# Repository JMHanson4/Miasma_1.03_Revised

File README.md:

# Miasma_1.03_Revised

***Note: use the BOM included in this repository.*** Some of the components have been relabelled in this revision so the BOM on SinPhi's website is no longer current.

The changes from version 1.03 are:

1) Updated the footprints and symbols to ones included in KiCAD 5.1.5, or otherwise included the auxillary libraries in the repository.

2) Made the 4QX output no longer inverted and added a jumper pin on the back that allows you to switch between (non-inverted) summing and 4QX modes.

3) Added diodes and jumper pins between the cycle gate input and trigger switch for each side. This allows you to choose whether applying a gate to the cycle input will cause it to start cycling automatically (jumper on) or require a trigger to start cycling (jumper off).

4) Fixed the EOC2 output from not being grounded.

5) Small tweaks such as adjusting track spacing, etc.

To do: the resistor in the feedback loop of the 4QX output amp (R67) should be shorted (solder bridge), not 220k. The purpose is to make this output stage a unity gain buffer instead of an amplifier; the 220k will cause the output to clip before the signal peak is reached. If you aren't using the 4QX feature then this is irrelevant.

# Acknowledgements

Original Miasma board by Sin Phi http://www.sinphi.com/synths/miasma/miasma.html, based on the Befaco Rampage http://www.befaco.org/rampage-2/. 4QX and diode mods inspired by Mcop http://www.mcop.co.uk/diy/mods-and-stripboard-layouts/miasma-function-generator-modifications/.

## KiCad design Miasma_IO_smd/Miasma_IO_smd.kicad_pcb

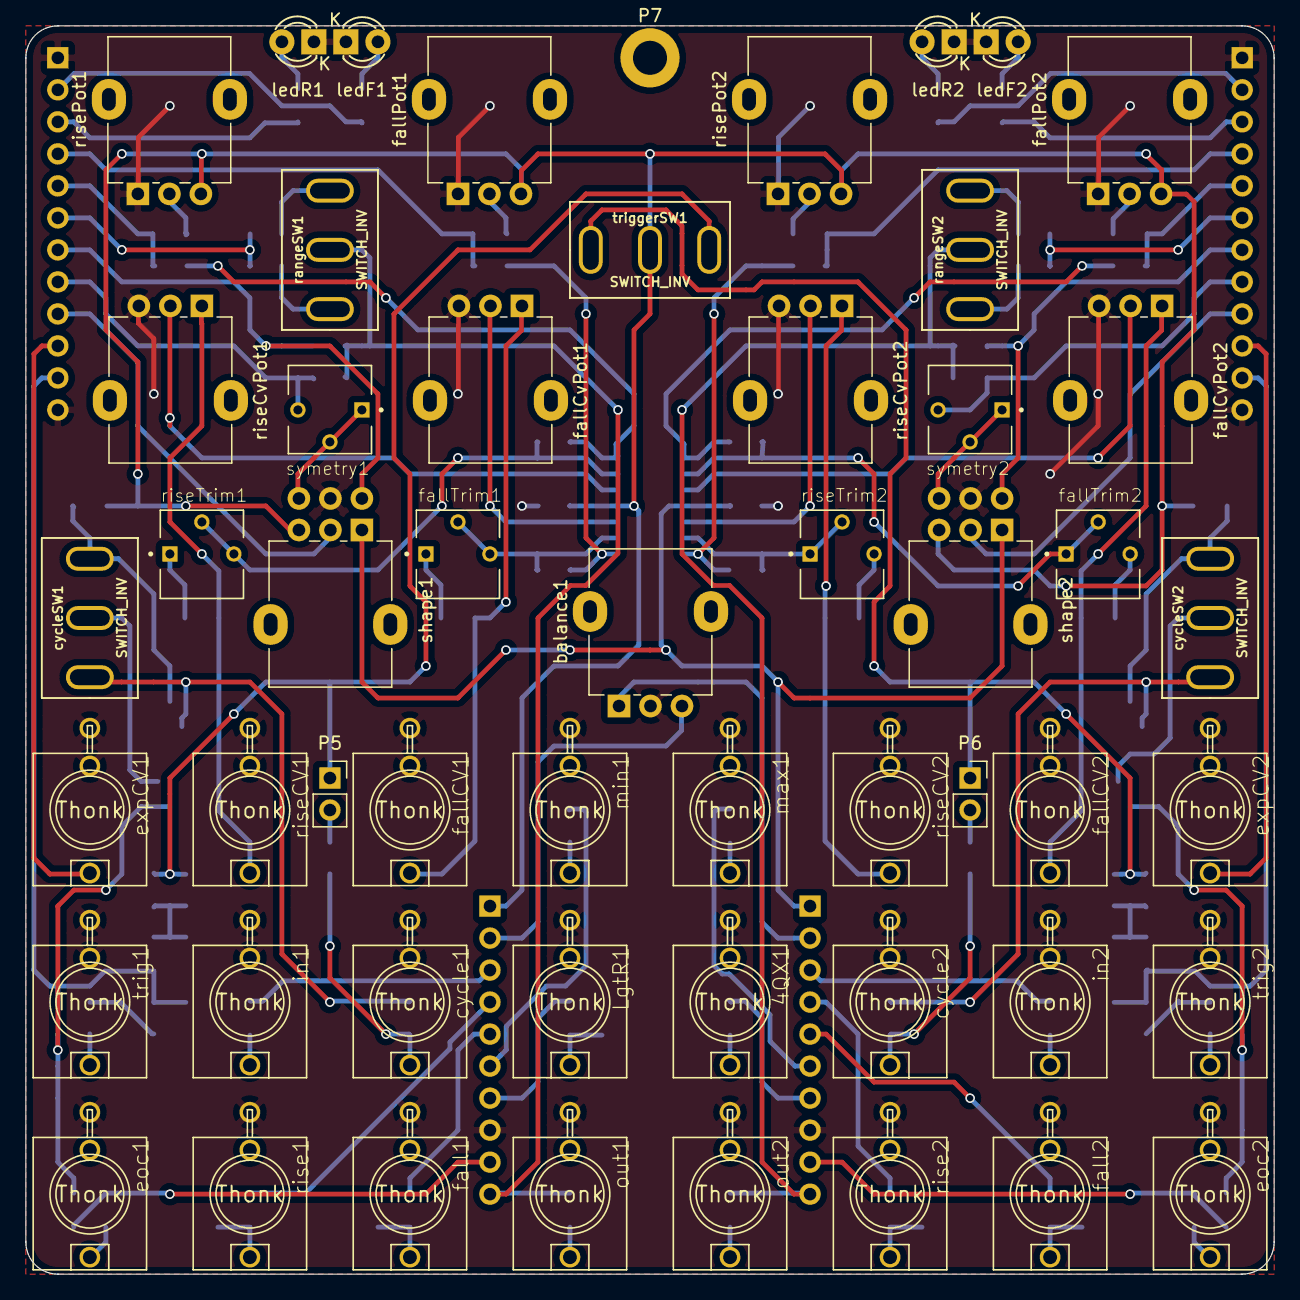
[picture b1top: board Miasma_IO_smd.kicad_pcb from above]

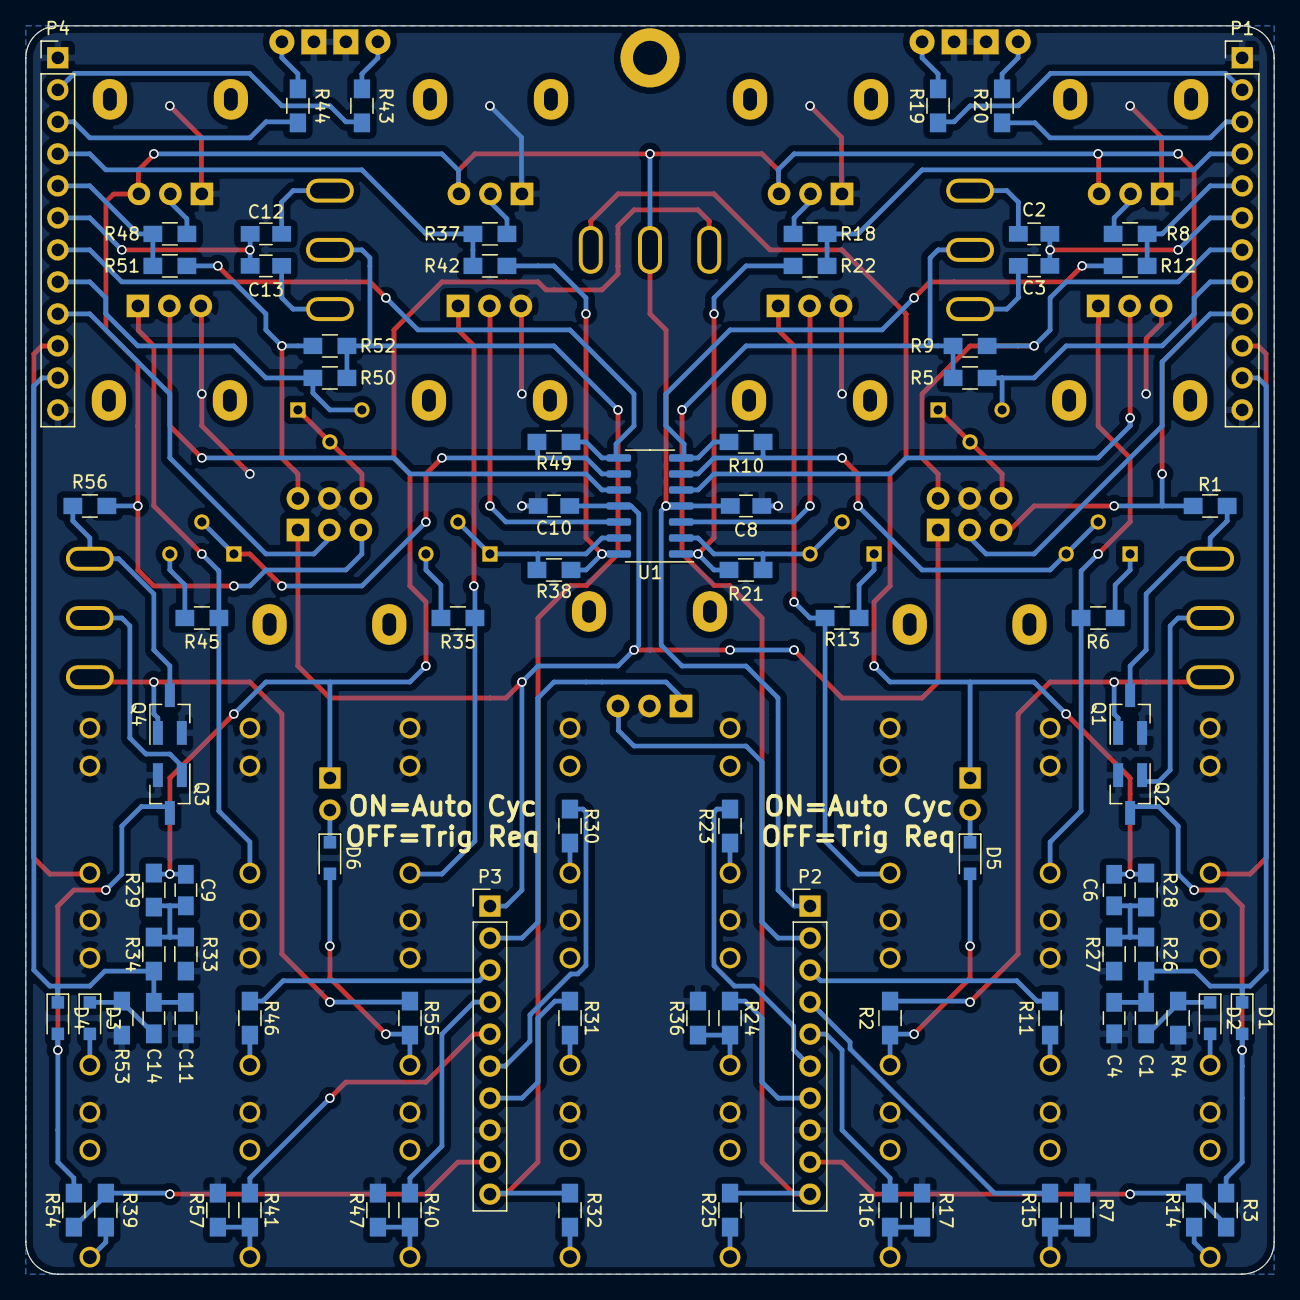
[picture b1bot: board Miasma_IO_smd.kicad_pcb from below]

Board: 2 copper layers, 99.1 x 99.1 mm, 137 parts (84 on the bottom side), 107 nets.

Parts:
4QX1: Thonk; WQP-PJ301M-12_JACK
C1, C4, C11, C14: 10n; C_0805_HandSoldering
C2, C12: 470n; C_0805_HandSoldering
C3, C13: 47n; C_0805_HandSoldering
C6, C9: 100n; C_0805_HandSoldering
C8, C10: 100nF; C_0805_HandSoldering
D1, D2, D3, D4, D5, D6: 1N4148WS; D_SOD-323_HandSoldering
LgtR1: Thonk; WQP-PJ301M-12_JACK
P1, P4: CONN_01X12; PinHeader_1x12_P2.54mm_Vertical
P2, P3: CONN_01X10; PinHeader_1x10_P2.54mm_Vertical
P5, P6: Conn_01x02; PinSocket_1x02_P2.54mm_Vertical
P7: CONN_01X01; MountingHole_2.7mm_M2.5_DIN965_Pad
Q1, Q2, Q3, Q4: MMBT3904; SOT-23_Handsoldering
R1, R3, R4, R27, R33, R53, R54, R56: 10k; R_0805_HandSoldering
R2, R10, R11, R12, R21, R22, R38, R42, R46, R49, R51, R55: 100k; R_0805_HandSoldering
R5, R9, R50, R52: 23k7; R_0805_HandSoldering
R6, R13, R35, R45: 47k; R_0805_HandSoldering
R7, R17, R36, R47, R57: 1M; R_0805_HandSoldering
R8, R18, R37, R48: 110k; R_0805_HandSoldering
R14, R15, R16, R23, R24, R25, R26, R30, R31, R32, R34, R39, R40, R41: 1k; R_0805_HandSoldering
R19, R20, R43, R44: 2k2; R_0805_HandSoldering
R28, R29: 4M7; R_0805_HandSoldering
U1: TL074; SOIC-14_3.9x8.7mm_P1.27mm
balance1: 1M; Potentiometer_Alpha_RD901F-40-00D_Single_Vertical
cycle1, cycle2: Thonk; WQP-PJ301M-12_JACK
cycleSW1, cycleSW2: SWITCH_INV; SPDT_Switch_P4.7mm
eoc1, eoc2: Thonk; WQP-PJ301M-12_JACK
expCV1, expCV2: Thonk; WQP-PJ301M-12_JACK
fall1, fall2: Thonk; WQP-PJ301M-12_JACK
fallCV1, fallCV2: Thonk; WQP-PJ301M-12_JACK
fallCvPot1, fallCvPot2: 100k; Potentiometer_Alpha_RD901F-40-00D_Single_Vertical
fallPot1, fallPot2: 100k; Potentiometer_Alpha_RD901F-40-00D_Single_Vertical
fallTrim1, fallTrim2: 100k; Bourns_3362P
in1, in2: Thonk; WQP-PJ301M-12_JACK
ledF1, ledF2: LED; LED-3MM
ledR1, ledR2: LED; LED-3MM
max1: Thonk; WQP-PJ301M-12_JACK
min1: Thonk; WQP-PJ301M-12_JACK
out1, out2: Thonk; WQP-PJ301M-12_JACK
rangeSW1, rangeSW2: SWITCH_INV; SPDT_Switch_P4.7mm
rise1, rise2: Thonk; WQP-PJ301M-12_JACK
riseCV1, riseCV2: Thonk; WQP-PJ301M-12_JACK
riseCvPot1, riseCvPot2: 100k; Potentiometer_Alpha_RD901F-40-00D_Single_Vertical
risePot1, risePot2: 100k; Potentiometer_Alpha_RD901F-40-00D_Single_Vertical
riseTrim1, riseTrim2: 100k; Bourns_3362P
shape1, shape2: 10K; Potentiometer_Alpha_RD902F-40-00D_Dual_Vertical
symetry1, symetry2: 10k; Bourns_3362P
trig1, trig2: Thonk; WQP-PJ301M-12_JACK
triggerSW1: SWITCH_INV; SPDT_Switch_P4.7mm

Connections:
4QX: P3.7, R31.1
EOC1: P2.9, R3.1, R14.2
EOC2: P3.9, R39.2, R54.1
Exp1: P1.10, expCV1.P$1
Exp2: P4.10, expCV2.P$1
Fall1: P2.5, R16.1
Fall2: P3.5, R41.1
FallCv1: P1.4, R18.2, R22.2
FallCv2: P4.5, R48.2, R51.2
GND: 4QX1.P$3, C4.2, C8.2, C10.2, C11.2, LgtR1.P$3, P1.1, P1.12, P2.8, P3.8, P4.1, P4.12, Q1.2, Q2.2, Q3.2, Q4.2, R4.2, R7.2, R17.2, R27.1, R33.1, R36.2, R47.2, R53.2, R57.2, balance1.2, cycle1.P$2, cycle1.P$3, cycle2.P$2, cycle2.P$3, eoc1.P$3, eoc2.P$3, expCV1.P$2, expCV1.P$3, expCV2.P$2, expCV2.P$3, fall1.P$3, fall2.P$3, fallCV1.P$2, fallCV1.P$3, fallCV2.P$2, fallCV2.P$3, fallCvPot1.3, fallCvPot2.3, fallPot1.1, fallPot2.1, in1.P$2, in1.P$3, in2.P$2, in2.P$3, ledF1.1, ledF2.1, ledR1.1, ledR2.1, max1.P$3, min1.P$3, out1.P$3, out2.P$3, rise1.P$3, rise2.P$3, riseCV1.P$2, riseCV1.P$3, riseCV2.P$2, riseCV2.P$3, riseCvPot1.3, riseCvPot2.3, risePot1.1, risePot2.1, shape1.5, shape2.5, trig1.P$2, trig1.P$3, trig2.P$2, trig2.P$3
In1: P2.3, R11.1
In2: P3.3, R46.1
L>R: P2.7, R24.1
Max: P3.6, R30.1
Min: P2.6, R23.1
unnamed: 4QX1.P$1, R31.2
unnamed: C1.1, D2.1, R4.1
unnamed: C2.2, rangeSW1.3
unnamed: C3.2, rangeSW1.1
unnamed: C6.2, R26.2, R27.2, R28.1
unnamed: C9.2, R29.1, R33.2, R34.2
unnamed: C12.2, rangeSW2.3
unnamed: C13.2, rangeSW2.1
unnamed: C14.1, D3.1, R53.1
unnamed: D1.2, Q2.3, R3.2
unnamed: D2.2, trig1.P$1
unnamed: D3.2, trig2.P$1
unnamed: D4.2, Q3.3, R54.2
unnamed: D5.1, P5.2
unnamed: D5.2, R2.2, cycle1.P$1
unnamed: D6.1, P6.2
unnamed: D6.2, R55.2, cycle2.P$1
unnamed: LgtR1.P$1, R24.2, R36.1
unnamed: P1.2, R19.1
unnamed: P1.3, R20.1
unnamed: P2.2, balance1.3
unnamed: P3.2, balance1.1
unnamed: P4.2, R43.1
unnamed: P4.3, R44.1
unnamed: Q1.1, R2.1, cycleSW1.1
unnamed: Q1.3, R1.2, cycleSW1.3
unnamed: Q2.1, cycleSW1.2
unnamed: Q3.1, cycleSW2.2
unnamed: Q4.1, R55.1, cycleSW2.1
unnamed: Q4.3, R56.2, cycleSW2.3
unnamed: R6.1, riseTrim1.1
unnamed: R6.2, riseCV1.P$1, riseCvPot1.1
unnamed: R8.1, risePot1.2
unnamed: R10.1, R12.1, U1.7
unnamed: R10.2, U1.6, riseTrim1.2, riseTrim1.3
unnamed: R11.2, in1.P$1
unnamed: R13.1, fallTrim1.1
unnamed: R13.2, fallCV1.P$1, fallCvPot1.1
unnamed: R14.1, eoc1.P$1
unnamed: R7.1, R15.1, rise1.P$1
unnamed: R16.2, R17.1, fall1.P$1
unnamed: R18.1, fallPot1.2
unnamed: R19.2, ledF1.2
unnamed: R20.2, ledR1.2
unnamed: R21.1, R22.1, U1.1
unnamed: R21.2, U1.2, fallTrim1.2, fallTrim1.3
unnamed: R23.2, min1.P$1
unnamed: R25.1, out1.P$1
unnamed: R30.2, max1.P$1
unnamed: R32.1, out2.P$1
unnamed: R35.1, riseTrim2.3
unnamed: R35.2, riseCV2.P$1, riseCvPot2.1
unnamed: R37.1, risePot2.2
unnamed: R38.1, R42.1, U1.14
unnamed: R38.2, U1.13, riseTrim2.1, riseTrim2.2
unnamed: R39.1, eoc2.P$1
unnamed: R40.2, R47.1, rise2.P$1
unnamed: R41.2, R57.1, fall2.P$1
unnamed: R43.2, ledR2.2
unnamed: R44.2, ledF2.2
unnamed: R45.1, fallTrim2.3
unnamed: R45.2, fallCV2.P$1, fallCvPot2.1
unnamed: R46.2, in2.P$1
unnamed: R48.1, fallPot2.2
unnamed: R49.1, R51.1, U1.8
unnamed: R49.2, U1.9, fallTrim2.1, fallTrim2.2
unnamed: U1.3, fallCvPot1.2
unnamed: U1.5, riseCvPot1.2
unnamed: U1.10, fallCvPot2.2
unnamed: U1.12, riseCvPot2.2
unnamed: shape1.6, symetry1.1, symetry1.2
unnamed: shape2.6, symetry2.1, symetry2.2
Out1: P2.10, R5.2, R9.2, R25.2, rangeSW1.2
Out2: P3.10, R32.2, R50.2, R52.2, rangeSW2.2
Rise1: P2.4, R15.2
Rise2: P3.4, R40.1
RiseCv1: P1.5, R8.2, R12.2
RiseCv2: P4.4, R37.2, R42.2
RngCap1: C2.1, C3.1, P1.6
RngCap2: C12.1, C13.1, P4.6
Sym1_1: P1.7, R9.1, shape1.4
Sym1_2: P4.7, R52.1, shape2.4
Sym2_1: P1.9, shape1.2
Sym2_2: P4.9, shape2.2
Sym3_1: P1.8, R5.1, symetry1.3
Sym3_2: P4.8, R50.1, symetry2.3
TRIG_SW1: C6.1, P5.1, R28.2, triggerSW1.3
TRIG_SW2: C9.1, P6.1, R29.2, triggerSW1.1
Trig1: C1.2, C4.1, D1.1, P1.11, R26.1
Trig2: C11.1, C14.2, D4.1, P4.11, R34.1
VCC: C8.1, P2.1, R1.1, R56.1, U1.4, fallPot1.3, fallPot2.3, risePot1.3, risePot2.3, shape1.3, shape2.3, triggerSW1.2
VEE: C10.1, P3.1, U1.11, shape1.1, shape2.1

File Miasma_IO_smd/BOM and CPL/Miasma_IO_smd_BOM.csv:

Comment,Designator,Footprint
SWITCH_INV,"cycleSW1,cycleSW2,rangeSW1,rangeSW2,triggerSW1",SPDT_Switch_P4.7mm
MMBT3904,"Q4,Q3,Q2,Q1",SOT-23_Handsoldering
10k,"symetry2,symetry1",Bourns_3362P
100k,"riseTrim2,riseTrim1,fallTrim2,fallTrim1",Bourns_3362P
Thonk,"trig2,trig1,riseCV2,riseCV1,rise2,rise1,out2,out1,min1,max1,LgtR1,in2,in1,fallCV2,fallCV1,fall2,fall1,expCV2,expCV1,eoc2,eoc1,cycle2,cycle1,4QX1",WQP-PJ301M-12_JACK
10K,"shape2,shape1",Potentiometer_Alpha_RD902F-40-00D_Dual_Vertical
100k,"risePot2,risePot1,riseCvPot2,riseCvPot1,fallPot2,fallPot1,fallCvPot2,fallCvPot1",Potentiometer_Alpha_RD901F-40-00D_Single_Vertical
1M,balance1,Potentiometer_Alpha_RD901F-40-00D_Single_Vertical
Conn_01x02,"P6,P5",PinSocket_1x02_P2.54mm_Vertical
1N4148WS,"D6,D5,D4,D3,D2,D1",D_SOD-323_HandSoldering
TL074,U1,SOIC-14_3.9x8.7mm_P1.27mm
CONN_01X12,"P4,P1",PinHeader_1x12_P2.54mm_Vertical
CONN_01X10,"P3,P2",PinHeader_1x10_P2.54mm_Vertical
LED,"ledF1,ledF2,ledR1,ledR2",LED-3MM
CONN_01X01,P7,MountingHole_2.7mm_M2.5_DIN965_Pad
10k,"R56,R54,R53,R33,R27,R4,R3,R1",R_0805_HandSoldering
100k,"R55,R51,R49,R46,R42,R38,R22,R21,R12,R11,R10,R2",R_0805_HandSoldering
23k7,"R52,R50,R9,R5",R_0805_HandSoldering
110k,"R48,R37,R18,R8",R_0805_HandSoldering
47k,"R45,R35,R13,R6",R_0805_HandSoldering
2k2,"R44,R43,R20,R19",R_0805_HandSoldering
1k,"R41,R40,R39,R34,R32,R31,R30,R26,R25,R24,R23,R16,R15,R14",R_0805_HandSoldering
4M7,"R29,R28",R_0805_HandSoldering
10n,"C14,C11,C4,C1",C_0805_HandSoldering
47n,"C13,C3",C_0805_HandSoldering
470n,"C12,C2",C_0805_HandSoldering
100n,"C9,C6",C_0805_HandSoldering
100nF,"C10,C8",C_0805_HandSoldering
1M,"R7,R17,R36,R47,R57",R_0805_HandSoldering

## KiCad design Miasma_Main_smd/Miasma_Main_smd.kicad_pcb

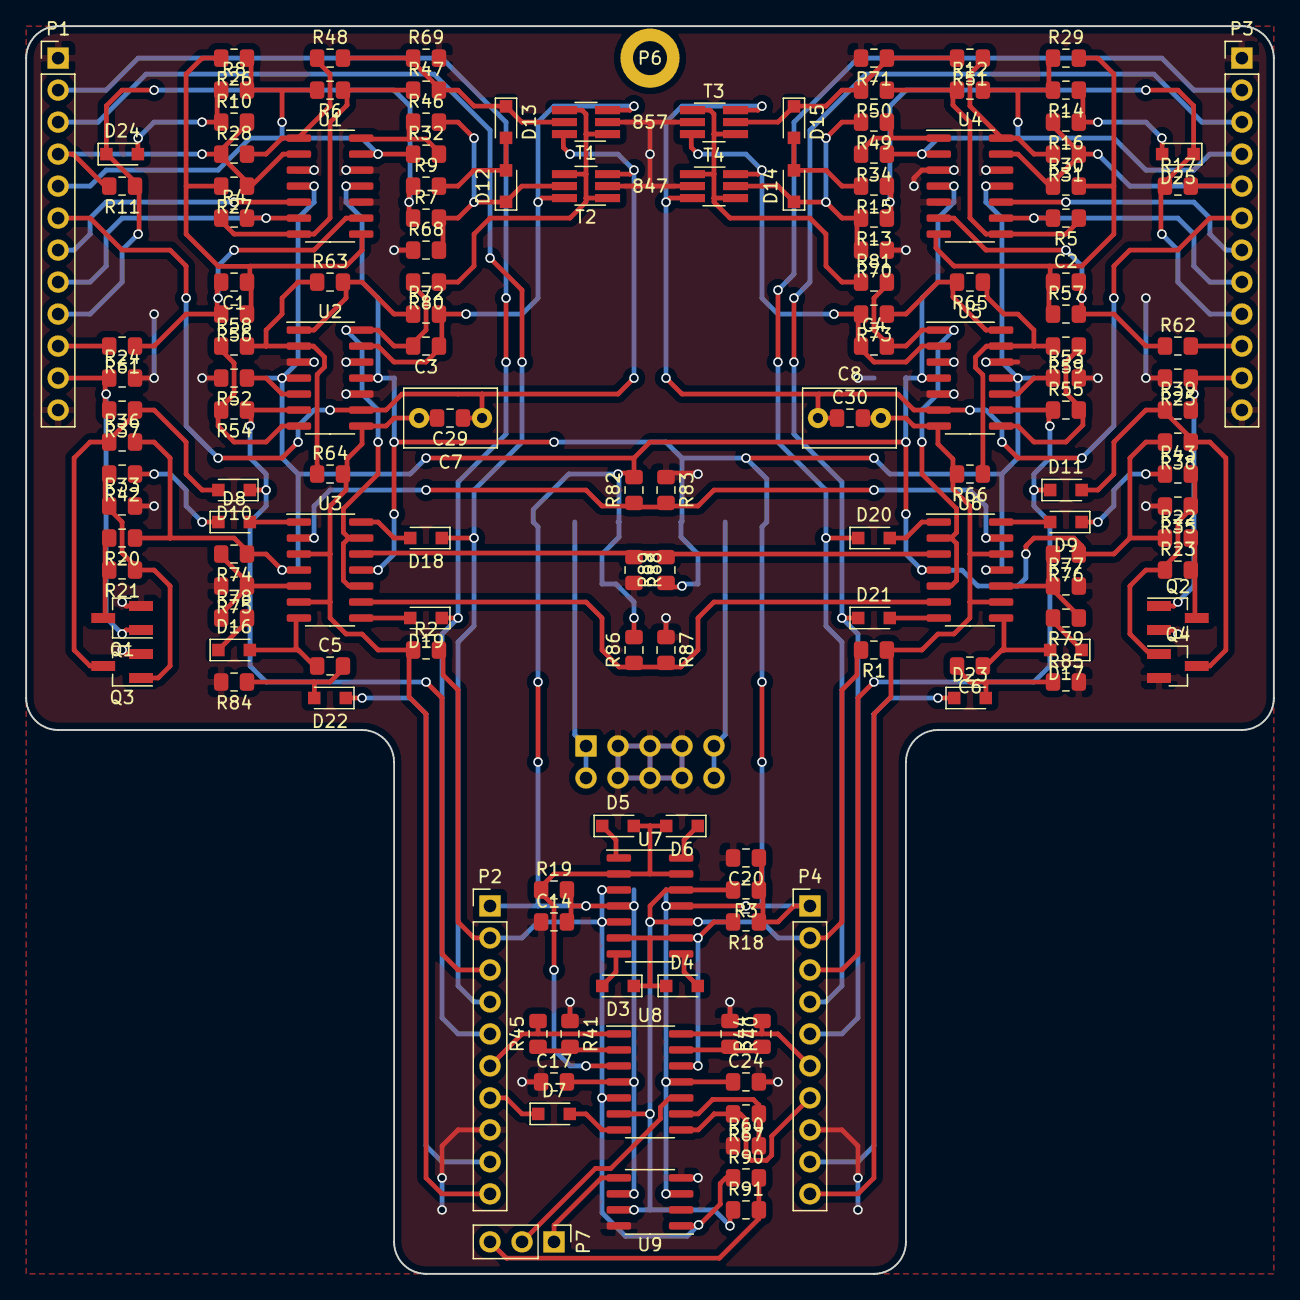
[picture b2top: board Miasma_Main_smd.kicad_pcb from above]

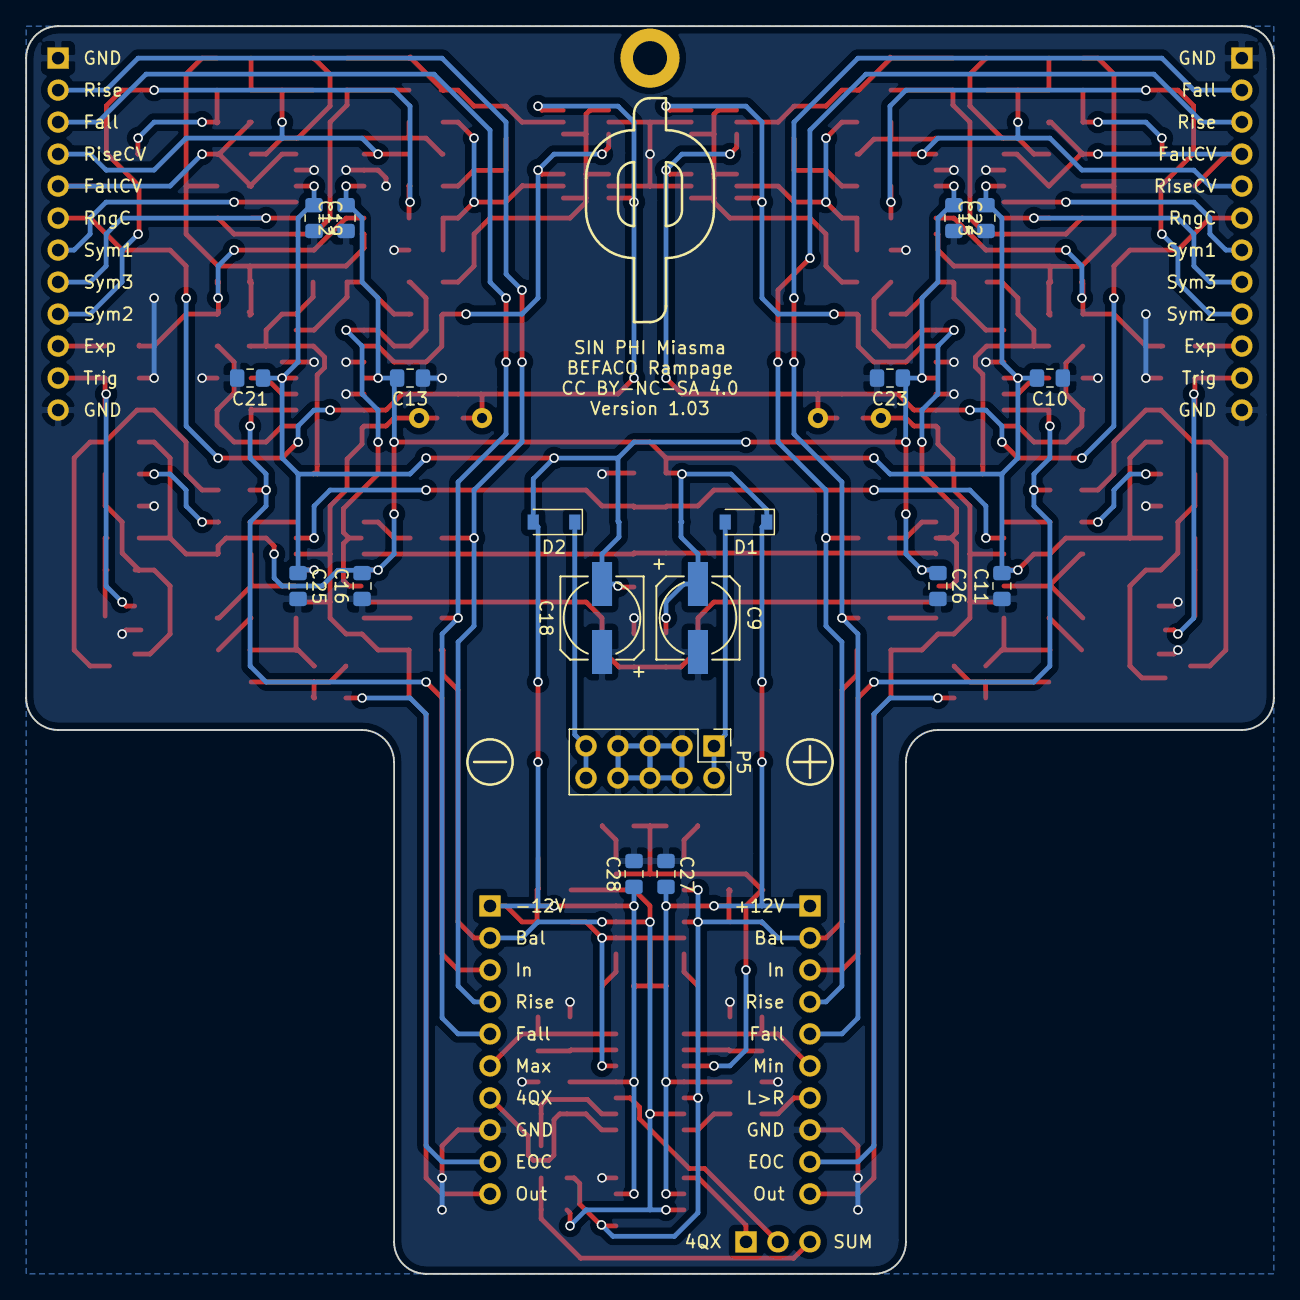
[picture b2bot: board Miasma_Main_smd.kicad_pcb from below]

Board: 2 copper layers, 99.1 x 99.1 mm, 170 parts (19 on the bottom side), 107 nets.

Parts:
C1, C2: 560p; C_0805_2012Metric_Pad1.15x1.40mm_HandSolder
C3, C4: 100p; C_0805_2012Metric_Pad1.15x1.40mm_HandSolder
C5, C6, C10, C11, C12, C13, C14, C15, C16, C17, C19, C20, C21, C22, C23, C24, C25, C26, C27, C28: 100n; C_0805_2012Metric_Pad1.15x1.40mm_HandSolder
C7, C8: 2n2 (PP); C_Rect_L7.2mm_W4.5mm_P5.00mm_FKS2_FKP2_MKS2_MKP2
C9, C18: 10u; c_elec_6.3x5.8
C29, C30: 1n; C_0805_2012Metric_Pad1.15x1.40mm_HandSolder
D1, D2: 1N5819HW; D_SOD-123
D3, D4, D5, D6, D7, D8, D9, D10, D11, D12, D13, D14, D15, D16, D17, D18, D19, D20, D21, D22, D23, D24, D25: 1N4148WS; D_SOD-323_HandSoldering
P1, P3: CONN_01X12; PinHeader_1x12_P2.54mm_Vertical
P2, P4: CONN_01X10; PinHeader_1x10_P2.54mm_Vertical
P5: CONN_02X05; PinHeader_2x05_P2.54mm_Vertical
P6: CONN_01X01; MountingHole_2.7mm_M2.5_DIN965_Pad
P7: SUM_or_4QX; PinHeader_1x03_P2.54mm_Vertical
Q1, Q2, Q3, Q4: MMBT3904; SOT-23_Handsoldering
R1, R2, R40, R41: 30k; R_0805_2012Metric_Pad1.15x1.40mm_HandSolder
R3: 10M; R_0805_2012Metric_Pad1.15x1.40mm_HandSolder
R4, R5, R21, R23, R37, R39, R42, R43, R44, R45, R58, R59, R64, R66, R86, R89: 10k; R_0805_2012Metric_Pad1.15x1.40mm_HandSolder
R6, R12, R26, R27, R28, R29, R30, R31, R32, R33, R34, R35, R46, R47, R48, R49, R50, R51, R52, R53, R54, R55, R56, R57, R60, R78, R79, R83, R90, R91: 100k; R_0805_2012Metric_Pad1.15x1.40mm_HandSolder
R7, R11, R13, R17, R24, R25: 560k; R_0805_2012Metric_Pad1.15x1.40mm_HandSolder
R8, R10, R14, R16: 3M; R_0805_2012Metric_Pad1.15x1.40mm_HandSolder
R9, R15, R18, R19, R74, R76: 1M; R_0805_2012Metric_Pad1.15x1.40mm_HandSolder
R20, R22, R36, R38: 4k7; R_0805_2012Metric_Pad1.15x1.40mm_HandSolder
R61, R62, R80, R81: 110k; R_0805_2012Metric_Pad1.15x1.40mm_HandSolder
R63, R65: 180k; R_0805_2012Metric_Pad1.15x1.40mm_HandSolder
R67: 220k; R_0805_2012Metric_Pad1.15x1.40mm_HandSolder
R68, R69, R70, R71: 2k2; R_0805_2012Metric_Pad1.15x1.40mm_HandSolder
R72, R73: 470k; R_0805_2012Metric_Pad1.15x1.40mm_HandSolder
R75, R77: 22k; R_0805_2012Metric_Pad1.15x1.40mm_HandSolder
R82: 20k; R_0805_2012Metric_Pad1.15x1.40mm_HandSolder
R84, R85, R87, R88: 1k; R_0805_2012Metric_Pad1.15x1.40mm_HandSolder
T1, T3: BCM857DS; TSOT-23-6_HandSoldering
T2, T4: BCM847DS; TSOT-23-6_HandSoldering
U1, U2, U3, U4, U5, U6, U7, U8: TL074; SOIC-14_3.9x8.7mm_P1.27mm
U9: AD633; SOIC-8_3.9x4.9mm_P1.27mm

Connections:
4QX: P4.7, R67.2, U8.8
+1.2V: R86.1, R87.2, U3.9, U6.6
+2.4V: R82.1, R83.2, U3.2, U6.13
-1.2V: R88.1, R89.2, U3.12, U6.3
Bal1: P2.2, R2.2, R90.1, U7.3, U7.5, U8.5, U9.1
Bal2: P4.2, R1.2, R3.2, R91.1, U7.10, U7.12, U8.6, U9.7
EOC1: D22.1, P2.9
EOC2: D23.1, P4.9
Exp1: P1.10, R61.2
Exp2: P3.10, R62.2
Fall1: D19.1, P1.2, P2.5
Fall2: D21.1, P3.3, P4.5
FallCv1: P1.4, R10.2, R11.2, R27.1, R28.1, U1.2
FallCv2: P3.5, R16.2, R17.2, R30.1, R31.1, U4.13
GND: C9.2, C10.1, C11.1, C12.1, C13.1, C14.1, C15.1, C16.1, C17.1, C18.1, C19.2, C20.2, C21.2, C22.2, C23.2, C24.2, C25.2, C26.2, C27.1, C28.2, P1.1, P1.12, P2.8, P3.1, P3.12, P4.8, P5.3, P5.4, P5.5, P5.6, P5.7, P5.8, Q1.2, Q2.2, Q3.2, Q4.2, R24.2, R25.2, R33.2, R35.2, R40.1, R41.1, R52.2, R53.2, R60.1, R68.1, R69.2, R70.1, R71.2, R75.2, R77.2, R83.1, R84.2, R85.2, R87.1, R88.2, T1.2, T2.2, T3.2, T4.2, U1.3, U1.10, U1.12, U2.3, U2.10, U2.12, U4.3, U4.5, U4.12, U5.3, U5.5, U5.12, U9.2, U9.4, U9.8
In1: D10.1, P2.3, R54.1, U2.6
In2: D11.1, P4.3, R55.1, U5.9
L>R: D7.1, P2.7
Max: P4.6, R44.2, U8.14
Min: P2.6, R45.2, U8.1
unnamed: C1.1, R26.2, R27.2, R56.1, U1.8
unnamed: C1.2, R56.2, R61.1, U1.9
unnamed: C2.1, R29.2, R30.2, R57.1, U4.7
unnamed: C2.2, R57.2, R62.1, U4.6
unnamed: C3.1, R72.2, T1.3, T2.6, U2.13
unnamed: C3.2, R80.2, U2.14, U3.10, U3.13
unnamed: C4.1, R73.2, T3.3, T4.6, U5.2
unnamed: C4.2, R81.2, U5.1, U6.2, U6.5
unnamed: C5.1, D16.2, U3.7
unnamed: C5.2, D22.2, R84.1
unnamed: C6.1, D17.2, U6.8
unnamed: C6.2, D23.2, R85.1
unnamed: D1.2, P5.1, P5.2
unnamed: D2.1, P5.9, P5.10
unnamed: D3.1, D4.1, R18.2, U7.6, U7.9, U8.12
unnamed: D3.2, U7.7
unnamed: D4.2, U7.8
unnamed: D5.1, U7.1
unnamed: D5.2, D6.2, R19.1, U7.2, U7.13, U8.3
unnamed: D6.1, U7.14
unnamed: D7.2, U8.7
unnamed: D8.1, R42.1
unnamed: D8.2, U3.1
unnamed: D9.1, R43.1
unnamed: D9.2, U6.14
unnamed: D10.2, Q3.3, R36.1, R37.1
unnamed: D11.2, Q4.3, R38.1, R39.1
unnamed: D12.1, R7.2, R46.2, R68.2, T2.5
unnamed: D12.2, D13.2, R9.2
unnamed: D13.1, R47.2, R48.2, R69.1, T1.5
unnamed: D14.1, R13.2, R49.2, R70.2, T4.5
unnamed: D14.2, D15.2, R15.2
unnamed: D15.1, R50.2, R51.2, R71.1, T3.5
unnamed: D16.1, R78.2
unnamed: D17.1, R79.2
unnamed: D18.2, U3.14
unnamed: D19.2, U3.8
unnamed: D20.2, U6.1
unnamed: D21.2, U6.7
unnamed: D24.2, R8.1, R10.1
unnamed: D25.2, R14.1, R16.1
unnamed: P7.1, U9.5
unnamed: P7.2, U8.10
unnamed: P7.3, R90.2, R91.2
unnamed: Q1.3, R20.2, R21.2
unnamed: Q2.3, R22.2, R23.2
unnamed: Q3.1, R21.1, R33.1, R42.2
unnamed: Q4.1, R23.1, R35.1, R43.2
unnamed: R4.1, R6.1, R47.1, U1.7
unnamed: R5.1, R12.1, R50.1, U4.8
unnamed: R28.2, R48.1, U1.1
unnamed: R31.2, R51.1, U4.14
unnamed: R32.2, R46.1, U1.14
unnamed: R34.2, R49.1, U4.1
unnamed: R40.2, R44.1, U8.13
unnamed: R41.2, R45.1, U8.2
unnamed: R52.1, U2.5
unnamed: R53.1, U5.10
unnamed: R54.2, R58.1, U2.7
unnamed: R55.2, R59.1, U5.8
unnamed: R58.2, R63.1, R64.1, U2.2
unnamed: R59.2, R65.1, R66.1, U5.13
unnamed: R60.2, R67.1, U8.9
unnamed: R63.2, R72.1, U2.1
unnamed: R65.2, R73.1, U5.14
unnamed: R74.2, R75.1, R78.1, U3.5
unnamed: R76.2, R77.1, R79.1, U6.10
unnamed: R80.1, T1.1, T1.4, T2.1, T2.4
unnamed: R81.1, T3.1, T3.4, T4.1, T4.4
Out1: C7.2, C29.2, P2.10, R2.1, R64.2, U2.8, U3.3, U3.6
Out2: C8.2, C30.2, P4.10, R1.1, R66.2, U5.7, U6.9, U6.12
Rise1: D18.1, P1.3, P2.4
Rise2: D20.1, P3.2, P4.4
RiseCv1: P1.5, R6.2, R8.2, R26.1, R32.1, U1.13
RiseCv2: P3.4, R12.2, R14.2, R29.1, R34.1, U4.2
RngCap1: C7.1, C29.1, P1.6, T1.6, T2.3, U2.9
RngCap2: C8.1, C30.1, P3.6, T3.6, T4.3, U5.6
Sym1_1: P1.7, U1.5
Sym1_2: P3.7, U4.10
Sym2_1: D24.1, P1.9, R7.1, R9.1, R11.1
Sym2_2: D25.1, P3.9, R13.1, R15.1, R17.1
Sym3_1: P1.8, R4.2, U1.6
Sym3_2: P3.8, R5.2, U4.9
Trig: P3.11, Q2.1, R25.1, R39.2
Trig1: P1.11, Q1.1, R24.1, R37.2
VCC: C9.1, C10.2, C11.2, C12.2, C13.2, C14.2, C15.2, C16.2, C17.2, C27.2, D1.1, P2.1, R19.2, R20.1, R22.1, R36.2, R38.2, R74.1, R76.1, R82.2, R86.2, U1.4, U2.4, U3.4, U4.4, U5.4, U6.4, U7.4, U8.4, U9.6
VEE: C18.2, C19.1, C20.1, C21.1, C22.1, C23.1, C24.1, C25.1, C26.1, C28.1, D2.2, P4.1, R3.1, R18.1, R89.1, U1.11, U2.11, U3.11, U4.11, U5.11, U6.11, U7.11, U8.11, U9.3

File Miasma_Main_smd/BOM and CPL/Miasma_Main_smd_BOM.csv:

Comment,Designator,Footprint
BCM847DS,"T4,T2",TSOT-23-6_HandSoldering
BCM857DS,"T3,T1",TSOT-23-6_HandSoldering
MMBT3904,"Q4,Q3,Q2,Q1",SOT-23_Handsoldering
AD633,U9,SOIC-8_3.9x4.9mm_P1.27mm
1N4148WS,"D23,D22,D21,D20,D19,D18,D17,D16,D15,D14,D13,D12,D11,D10,D9,D8,D7,D6,D5,D4,D3,D25,D24",D_SOD-323_HandSoldering
TL074,"U8,U7,U6,U5,U4,U3,U2,U1",SOIC-14_3.9x8.7mm_P1.27mm
100k,"R91,R90,R83,R79,R78,R60,R57,R56,R55,R54,R53,R52,R51,R50,R49,R48,R47,R46,R35,R34,R33,R32,R31,R30,R29,R28,R27,R26,R12,R6",R_0805_2012Metric_Pad1.15x1.40mm_HandSolder
10k,"R89,R86,R66,R64,R59,R58,R45,R44,R43,R42,R39,R37,R23,R21,R5,R4",R_0805_2012Metric_Pad1.15x1.40mm_HandSolder
1k,"R88,R87,R85,R84",R_0805_2012Metric_Pad1.15x1.40mm_HandSolder
20k,R82,R_0805_2012Metric_Pad1.15x1.40mm_HandSolder
110k,"R81,R80,R62,R61",R_0805_2012Metric_Pad1.15x1.40mm_HandSolder
22k,"R77,R75",R_0805_2012Metric_Pad1.15x1.40mm_HandSolder
1M,"R76,R74,R19,R18,R15,R9",R_0805_2012Metric_Pad1.15x1.40mm_HandSolder
470k,"R73,R72",R_0805_2012Metric_Pad1.15x1.40mm_HandSolder
2k2,"R71,R70,R69,R68",R_0805_2012Metric_Pad1.15x1.40mm_HandSolder
220k,R67,R_0805_2012Metric_Pad1.15x1.40mm_HandSolder
180k,"R65,R63",R_0805_2012Metric_Pad1.15x1.40mm_HandSolder
30k,"R41,R40,R2,R1",R_0805_2012Metric_Pad1.15x1.40mm_HandSolder
4k7,"R38,R36,R22,R20",R_0805_2012Metric_Pad1.15x1.40mm_HandSolder
560k,"R25,R24,R17,R13,R11,R7",R_0805_2012Metric_Pad1.15x1.40mm_HandSolder
3M,"R16,R14,R10,R8",R_0805_2012Metric_Pad1.15x1.40mm_HandSolder
10M,R3,R_0805_2012Metric_Pad1.15x1.40mm_HandSolder
SUM_or_4QX,P7,PinHeader_1x03_P2.54mm_Vertical
1n,"C30,C29",C_0805_2012Metric_Pad1.15x1.40mm_HandSolder
100n,"C28,C27,C26,C25,C24,C23,C22,C21,C20,C19,C17,C16,C15,C14,C13,C12,C11,C10,C6,C5",C_0805_2012Metric_Pad1.15x1.40mm_HandSolder
100p,"C4,C3",C_0805_2012Metric_Pad1.15x1.40mm_HandSolder
560p,"C2,C1",C_0805_2012Metric_Pad1.15x1.40mm_HandSolder
CONN_02X05,P5,PinHeader_2x05_P2.54mm_Vertical
CONN_01X10,"P4,P2",PinHeader_1x10_P2.54mm_Vertical
CONN_01X12,"P3,P1",PinHeader_1x12_P2.54mm_Vertical
1N5819HW,"D2,D1",D_SOD-123
10u,"C9,C18",c_elec_6.3x5.8
CONN_01X01,P6,MountingHole_2.7mm_M2.5_DIN965_Pad

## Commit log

2020-07-18 Added through-hole footprints for C7/C8 (polypropylene timing caps)

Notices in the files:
Miasma_Main_smd/Miasma_Main_smd.kicad_pcb:
CC BY-NC-SA 4.0
